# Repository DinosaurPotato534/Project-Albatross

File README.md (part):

# Project Albatross

The goal for the project was to create an autonomous plane capable of flying for hours off of solar power. Another big aspect is the ability to takeoff from water using a pontoon system mounted to a 4-bar linkage. The plane is going to be made from foam board and 3d prints. The wingspan is 90in and the length is roughly 6ft. 

https://cad.onshape.com/documents/cb4d8119196719dc9005cd1f/w/a50220c0795171ae93763f3d/e/ee41d6fe8c21d3f854f1676d?renderMode=0&uiState=6aa1fe8d3db98abb8ad60905

## Motivation
We wanted to explore the idea of multi-hour flight using solar power. Most rc planes have a relatively short flight time, but we wanted to try and expand on that. That is why we also added the pontoons, so it could recharge on the surface of water.

## Design

### Pontoons
The pontoon mechanism works by having two hollow 3D printed hulls swing out when landing. The reason we decided to put them on a swinging mechanism was that it would greatly reduce drag, and in turn air resistance. Just based on frontal area that's around a 25% increase in efficiency. They will be driven by a motor that will winch it up or down.

### Solar Panels
The solar panels just sit on the wing and will be wired to an MPPT board. They each generate around 3.5W in full sun, and there will be 17. It should be enough to sustain flight, but it will almost never get perfect lighting, so we will see. These sit on a 90in wing that has an 7in chord (not including the ailerons). Panels measure 125mm, so roughly 5in.

### Hull
Used a series of ribs inside to support a really thin outer shell of 3D print. These will slide down into their corresponding spots, making the structure much stronger. The front one also serves as the motor mount too.

## PCB
### Flight Controller
The flight controller was built with Ardupilot in mind, with multiple connectors allowing for different sensors to be modular and  swapped out. It is designed to take a 3 or 4S battery, and runs on an STM32F405RGT6. We are planning on using a GPS and a magnetometer but we have extra connector for different sensors if we want to add them going forward. We also have an IMU and pressure sensor on the board.

### MPPT Board
We made a full solar circuit, with a MPPT board and BMI. With this plane design we kept the wings relatively small. Only 17 solar panels could fit. With each solar panel proving roughly 0.6V the total voltage was roughly 10V. This is well below the standard voltage of a 4s battery, thus we needed a step up MPPT board. The market for this is miniscule and expensive leading our design to be useful as it functioned as both a step up and step down board depending on the solar array. However, our board also ended up being far to expensive to become justifiable. We decided to pivot to using a standard step down MPPT and increasing the solar area, as well as deceasing the battery voltage to a 3S.

## Assembly 

### The Plane
Most of the planes assembly consists of techniques similar to other rc planes. The wings are made from foam board "wrapped" around a dowel spar. They are made by cutting 3 slits across a sheet of foam board spaced out at 7in, 8iin, and 17 from one end. Then the paper layer of the foam board is peeled off for the top of the airfoil to create a better curve. The foam board is folded over the wing spar and three sections of these are connected.

The body is made from a dowel as the main structure of the hull, with 3d printed shells for aerodynamics and part containers. The slide onto the dowel and will be hot glued into place. Then the electronics are wired and placed into the nose cone of the 3d printed hull. The pontoons can then be mounted on they're hinges, which will be connected to n20 motor to swing up and down.
Solar panels will be mounted on the wing using a plastic wrap to hold them in place, while still allowing sunlight through.

### The PCB
Both the pcbs, especially the mppt board, are rather complex and have a lot of smd soldering. The use of a hot plate will be need and following the design the components will be soldered on. These boards will then be wired and hooked up to the rest of the planes electronics.

## BOM

| Description                                                  | Quantity |    Price | Link                                                                                                                                                                                                                                                                                                                                                                                                                                                                                                                                                                                                                                                                    |
| ------------------------------------------------------------ | -------: | -------: | ----------------------------------------------------------------------------------------------------------------------------------------------------------------------------------------------------------------------------------------------------------------------------------------------------------------------------------------------------------------------------------------------------------------------------------------------------------------------------------------------------------------------------------------------------------------------------------------------------------------------------------------------------------------------- |
| Main Brushless Motor                                         |        0 |    19.98 | [View](https://www.amazon.com/D2830-Brushless-Multi-Copter-Fixed-Wing-Helicopters/dp/B0D3DTQCS6?crid=1GIDDJS7T4YGM&dib=eyJ2IjoiMSJ9.AtVN6vy-8eWpAr1MRXuwIyZDgROcZ_Tzuz1vBoY-LQgoGHMikw6Aqbtr0vY9_g7-KdBo8Uc5qtG9Z2M4y7HJNJ-4DeF8kwkHgLJEmAUFDxmb91PZrz4W3htgwBpbw4BqP0INFkJTwgfE83IHLo2A6Yt1P7s4NWxooXJ_7hyRbZfiLSRV9Om79zQwpNE-6LewTQ_vMCWp6zsd65cN0q3pzUgZFKQl49tTeJsKrsUk_vwhCnAS4FoziM5t2XskwUUXPg0w_hbD3VEKizfJy3LNRxQ9HERiJKMdJODfD9-f40Y.mDKjGPO2-bY4kN_1C4PMB4SJw4Vj_UEMF7pvPhxdHXQ&dib_tag=se&keywords=4s%2Bbrushless%2Bmotor&qid=1787538403&s=industrial&sprefix=4s%2Bbrushless%2Bmoto%2Cindustrial%2C144&sr=1-24&th=1)                                       |
| Propeller                                                    |        0 |     9.19 | [View](https://www.amazon.com/FOCMKEAS-Propeller-Control-Quadcopter-Propellers/dp/B0F7LGSVNX?dib=eyJ2IjoiMSJ9.A6pEEgKzE0xpVNJD1XzkBh2nzCzQmoNq3ytnVg6CN18DSJCYAb_vIOQs6C8UpuIxUIBGOFXvnDEB_UkNs5OgI2uLLwH9465pMMq5V0m_Dc9-5lnfrtW4XxR0hVYtef-Q3eX9Ex-b_6jeFyqg4qao58oj_oSJQ67rCSTJcOPaGaEuolYwWYajsof5d2b4Q7oDYOMhOJqfl2KeGGB-YOsVRt_N_G7Wvj5ITrCs1dr519pMPs-xR864BLOs0i2SqKWhch3QZd_lyTU7AmSTrIm3AY6-M7YS4UeShy5_y6pB76uU.ozcTE64lZMBamYODjHXiUzZvMs33qJ17Fo1byxuyLn0&dib_tag=se&keywords=10x7%2Bpropeller&qid=1787538510&sr=8-9&th=1)                                                                                                                                 |
| Light Weight PLA                                             |        1 |    29.99 | [View](https://www.amazon.com/Polymaker-PolyLite-LW-PLA-1-75mm-800g/dp/B09H2SC1CX?crid=2132M6YWZ9EGL&dib=eyJ2IjoiMSJ9.EbFv4lznFsPcWRDS9TjkviMWlq_K4jqpkA8IQc7o2zDEebKpblPqLRmth953MziS7uqHudJ0SZ3s5wBnAt_yUrxKvtQmWUkzZDUHRLlRxhPQMmJGF5JgJkjI19orItGwAG-fORcVH57sKaYh6ABwSmNhR0hW-JCWFJVTA7df6mxN11L5wEezJSx71Ra0gn5ADS7o05-v34wEVmZvxTj3QMUajjPENJMn1u_jx4HQ0n0.XZf55xAyfc2s93rCVnJll9koOeH9xDjBtNictLozpg4&dib_tag=se&keywords=pla%2Baero&qid=1787525308&sprefix=pla%2Baero%2Caps%2C175&sr=8-2&th=1)                                                                                                                                                                 |
| Solar Panels                                                 |       30 |        4 | [View](https://www.ebay.com/itm/382873833299?_trksid=p2332490.c101224.m-1&var=651906635231)                                                                                                                                                                                                                                                                                                                                                                                                                                                                                                                                                                             |
| Servos (5 Pack)                                              |        1 |    15.99 | [View](https://www.amazon.com/dp/B0BWJ2CK9D?_encoding=UTF8&th=1)                                                                                                                                                                                                                                                                                                                                                                                                                                                                                                                                                                                                        |
| Servo Extention Cables                                       |        1 |     9.99 | [View](https://www.amazon.com/ACEIRMC-Extension-Connector-Airplanes-Control/dp/B0CP7FRV31?crid=208A8HM7J7RMB&dib=eyJ2IjoiMSJ9.zvspaGyYEhj8FE188_ucmxEkKO9qxdxkeWBVjVOxg_IdOeuFNdGl7vn5_YA_3SkekBpo1C4ZVZeYne-sWa-vqcT14DQGpfkZP0DvSsxYqCkKgQiqMDOEiCSFFEm6DgK3rqWCAZoQL5KlCa5mTqUZ2ex7WquiyLc5CjRFcVyx7MRTT2iRXcr1xalmlWvPcaOSW3QRbxB1vWPW9z5XEMp2abnEaBUddNU7IUBYtHoYaUeh_4k-P5CyB4RuSx_zgH8jz7q1C9rbM7gXJz2oLb_1u9YX6dsfYdR8L4PDelta2Ic.q6GoTBJ_aluZ2bmCM-GL7KpXotR3rhAZuRiR03xYp-Y&dib_tag=se&keywords=servo%2Bextension%2Bcable%2B3ft&qid=1787525999&sprefix=servo%2Bextension%2Bcable%2B3ft%2Caps%2C156&sr=8-2&th=1)                                               |
| 3S Lipo                                                      |        0 |    16.99 | [View](https://www.amazon.com/2200mAh-Connector-Airplane-Quadcopter-Helicopter/dp/B08CZF373Y?dib=eyJ2IjoiMSJ9.qVFbEjwkpjGPTIbNqqaG4vhhEhuTYIhbIrznxJf2mWbGQFAQZzQvMC-RFV3-_m0Y3fUMGU2WUniptrScL0GNg0JNWvpu92oegfyhtbsOfVlIXlQ-MSGKUgVLKmpeuwx3UI1lsvJuu8vqa-Yaq4HsqnQAZZ_Rz_IvS5CB1vaPLZo0VIJ8n6EhUtJ7-DbkXdtaIhPBBi96NDbnM-Gm8rh9aLTVWOSHBg1nrYiUrKQ3GgO3EjhKp2QWHQe2iZsrDUKseEFkoB9d_mDGmAwJTdDD2BOaxg-PfcvtzBMpGu8Q-8.kPC3qnyTph9ywtksvaFng7sRWRmlsHQLAdpGe4SUKuI&dib_tag=se&keywords=3s%2Blipo%2Bbattery%2B2200mah%2Bturnigy&qid=1788917182&sr=8-5&th=1)                                                                                                            |
| ESC                                                          |        0 |     28.4 | [View](https://www.amazon.com/60A-Brushless-Fixed-Wing-Aircraft-Helicopter/dp/B0FRM7X984?crid=3PJRS2ICQ8PJD&dib=eyJ2IjoiMSJ9.l-i8O1etdcDAwANXbMuoWiZWPcCDAv0Sbts3AtoG4644KeM131bYEzrw-p2MOpDivXIBVtqrIHys9zYjqJ12LKnK6i-6AH8XN9EJTKXhXk6bnEsInO310qC9xtRnb-KxAyLtBdO-nKIXAzmh6S25dI1q8qE13uXMczSF6lAoa4Z5NEnQ1c-VgTorYn7Om1HT8OKtg7QFZ9L8LORe08OILE3gtEbHjzeyqic_LyjKrPWg9aB3qZkXp0HWgDVTno_lIJrRG5CHcl-eH1EkQ6-XxLoF0CTAm4u7tXZE4JOihRc.F29bWjkF8PrGOvVfpu0PWkPe3OBKBhs2UlFD32E6XW8&dib_tag=se&keywords=60A%2Besc&qid=1787538359&sprefix=60a%2Bes%2Caps%2C204&sr=8-4&th=1)                                                                                             |
| Heat Set Inserts                                             |        1 |     4.99 | [View](https://www.amazon.com/Aoserge-100Pcs-Brass-Heat-Inserts/dp/B0FM45X5TD?crid=18SC6KZP9OQV&dib=eyJ2IjoiMSJ9.yMovo3L8gJsoYK8w4IEzTWAA8Pa8BA9cJIQ-iAF8utzPJ714NxCnewEAb7-vQQ4wjrNfGFI7i-OyntuQi7irDqRP6uR-vwBS8VsjYbYfnEGw1HEHWc_urtRw7aOZabJ8nMm7X1PGJRnSm_dumVbfvMLHscQXXEKbt6OXNfPWSSik5vOfFX9qPY9pHfWj4SHEL0ygbkMKETaEilfUxx_5VjPdDVNT5e97h0AJBQlPIaQ.5RN2Lr60uWhE16Ea_KMSffw7Fy3fc5X4_u3aus6Fmds&dib_tag=se&keywords=heat%2Bset%2Binserts&qid=1788233777&refinements=p_36%3A-1000&rnid=386419011&sprefix=heat%2Bset%2Binsert%2Caps%2C177&sr=8-8&th=1)                                                                                                           |
| M3 Screws                                                    |        1 |     6.99 | [View](https://www.amazon.com/Machine-Assorted-Assortment-Stainless-Threaded/dp/B0DFWX8F36?crid=2IMXPAP1DEIAP&dib=eyJ2IjoiMSJ9.yZ4b1PXj7_4Gv5y9TnkcPHKxO-JQ9HyV9zOqDs1Fm5YNqA9myOSVzQR86Kytn6L07abLABHcaVdUCsevvHmGTXOa28JjPYt_5xii7wxPjRW9afO-sCb8yxQ4SSXCAAmo9bffwnMVAzJu2TboclRhZvmMOorqYb0dWacgTGgbutoSSJYu1r2_nygjP9LcBysSyQC3k7f4e7l_HnsZ61rrlNLoYdkTnklYXdqPEj5ZLEU.NHmRGP9EbYvQucNLRHm8Z_QKjKLUAvDfJK4pTsFrj0Y&dib_tag=se&keywords=m3%2Bscrews&qid=1787538716&refinements=p_36%3A-1000&rnid=2661611011&sprefix=m3%2Bscrew%2Caps%2C168&sr=8-9&th=1)                                                                                                              |
| Controller                                                   |        0 |    54.89 | [View](https://www.amazon.com/FLYSKY-Transmitter-Controller-Receiver-Upgrade/dp/B07Z8VCB45?crid=31XOXYXMOF57J&dib=eyJ2IjoiMSJ9.oYVOZgIKCn7QHiQW_sPBdqCzg8t7x423ixB_IW4cyeVR8NzFLb4Va8IOe6aXXys3DgsJLeYg0AZj4C6nYi5yfUcnhJPpvlJfRvaaQPgnwUMt_mnDe2qD3gG-DdXs-hZiZr7JC06yUwYZu2FwEhZMYXUMUlfIZ3HLRCX-9MHtBgzPtYGTfMZA61y8FiqHdAbDZFId_eyTI-cYJqWUszTLyqKt7BXOan2ybAT59q5ePnzmNrsKFerFJt5INTKZUfP-MXZW1UjR8EVU4ZrsCfYvvbbefuqou7SJWZUwxCtYB74.GyGO-L0K5NV1BGEOLjfxkipUgwNBX3knqvS8UBxhQLE&dib_tag=se&keywords=fly+sky+controller&qid=1787538836&sprefix=fly+sky+co%2Caps%2C176&sr=8-1)                                                                                     |
| Foam Board                                                   |       10 |     1.25 | [View](https://www.dollartree.com/readi-board-white-foam-boards/809955)                                                                                                                                                                                                                                                                                                                                                                                                                                                                                                                                                                                                 |
| N20 Motor                                                    |        4 |     4.17 | [View](https://www.aliexpress.us/item/3256803908995996.html?spm=a2g0o.productlist.main.1.204626f5A7Jdmy&algo_pvid=8b3a0dbe-85eb-467c-8fe9-f87f66337553&algo_exp_id=8b3a0dbe-85eb-467c-8fe9-f87f66337553-0&pdp_ext_f=%7B%22order%22%3A%221694%22%2C%22eval%22%3A%221%22%2C%22fromPage%22%3A%22search%22%7D&pdp_npi=6%40dis%21USD%213.68%210.99%21%21%213.68%210.99%21%40210328c017889213388988109e0e7d%2112000028016789215%21sea%21US%210%21ABX%211%210%21n_tag%3A-29910%3Bd%3Ac2c1a869%3Bm03_new_user%3A-29895%3BpisId%3A5000000210782938&curPageLogUid=oM71zmsPOiT8&utparam-url=scene%3Asearch%7Cquery_from%3A%7Cx_object_id%3A1005004095310748%7C_p_origin_prod%3A)   |
| GPS                                                          |        1 |     15.9 | [View](https://robofusion.net/products/mg-a01-gps-module)                                                                                                                                                                                                                                                                                                                                                                                                                                                                                                                                                                                                               |
| Telemetry                                                    |        1 |     65.9 | [View](https://robofusion.net/products/micoair-lr900-p-915mhz-lora-telemetry-radio-for-pixhawk-ardupilot-px4-1w-fhss-flagship-long-range-pair?variant=54111278530879)                                                                                                                                                                                                                                                                                                                                                                                                                                                                                                   |
| BMS                                                          |        1 |     1.13 | [View](https://www.aliexpress.us/item/3256807501448998.html?spm=a2g0o.productlist.main.24.77ec3d62baKU9j&algo_pvid=bad08f0c-8228-4e05-bf4c-bcd4cd963110&algo_exp_id=bad08f0c-8228-4e05-bf4c-bcd4cd963110-21&pdp_ext_f=%7B%22order%22%3A%22928%22%2C%22eval%22%3A%221%22%2C%22fromPage%22%3A%22search%22%7D&pdp_npi=6%40dis%21USD%211.13%210.99%21%21%217.56%216.62%21%402101c4b817889206645041384e0e0f%2112000041841194925%21sea%21US%210%21ABX%211%210%21n_tag%3A-29910%3Bd%3Ac2c1a869%3Bm03_new_user%3A-29895%3BpisId%3A5000000210782938&curPageLogUid=EdmXCWhx64s9&utparam-url=scene%3Asearch%7Cquery_from%3A%7Cx_object_id%3A1005007687763750%7C_p_origin_prod%3A)  |
| MPPT Board                                                   |        1 |    20.41 | [View](https://www.aliexpress.us/item/3256810455381147.html?spm=a2g0o.productlist.main.5.1764tsWXtsWXhf&algo_pvid=96684140-d778-43dc-ac98-f4994373f856&algo_exp_id=96684140-d778-43dc-ac98-f4994373f856-4&pdp_ext_f=%7B%22order%22%3A%2212%22%2C%22eval%22%3A%22%22%2C%22fromPage%22%3A%22search%22%7D&pdp_npi=6%40dis%21USD%2120.41%2113.28%21%21%21136.26%2188.66%21%402101ca9517889202540843342e0eab%2112000053059870601%21sea%21US%210%21ABX%211%210%21n_tag%3A-29910%3Bd%3Ac2c1a869%3Bm03_new_user%3A-29895%3BpisId%3A5000000210782933&curPageLogUid=7y9B1Ewqa6k0&utparam-url=scene%3Asearch%7Cquery_from%3A%7Cx_object_id%3A1005010641695899%7C_p_origin_prod%3A) |
| passive piezo                                                |        5 |   0.4017 | [View](https://www.lcsc.com/product-detail/C128650.html?s_z=n_q_C128650&globalKeyword=C128650)                                                                                                                                                                                                                                                                                                                                                                                                                                                                                                                                                                          |
| 100u/35V poly                                                |       50 |   0.0139 | [View](https://www.lcsc.com/product-detail/C14663.html?s_z=n_q_CC0603KRX7R9BB104&spm=wm.fly.bg.0.xh&lcsc_vid=ElFaA1QDFFgKXlQHFFINU1JeFlZaUF0FQFNdXlUFEgUxVlNeT1ZcVldQRlleXzsOAxUeFF5JWBYZEEoKFBINSQcJGk4%3D)                                                                                                                                                                                                                                                                                                                                                                                                                                                            |
| 100n/50V 0603                                                |       10 |   0.2003 | [View](https://www.lcsc.com/product-detail/Multilayer-Ceramic-Capacitors-MLCC-SMD-SMT_Taiyo-Yuden-TMK325BJ106KN-T_C92834.html)                                                                                                                                                                                                                                                                                                                                                                                                                                                                                                                                          |
| 10u/25V 1210                                                 |       10 |   0.2257 | [View](https://www.lcsc.com/product-detail/C92771.html?s_z=n_q_Taiyo%2520Yuden%2520EMK325BJ226MD-T&spm=wm.fly.bg.0.xh&lcsc_vid=FANdVwJVQgMLV11TTlQPX1UHRlFcBlFQRlEMBFYDE1kxVlNeT1ddUlVRQFZYUDsOAxUeFF5JWBYZEEoKFBINSQcJGk4eFQsCAgIaSgADAwAHC0sLAg0aDggHDgQcSgcDBQADDgdLFAAeBgcPAw4cFEkLGwINShcLE0wdChA5AwAHHgtLDhQKAgpLEgwFVFZTFQtcVVILE0waOCdfRVZZVkoOAwwC)                                                                                                                                                                                                                                                                                                            |
| 22u/16V 1210                                                 |       20 |   0.0291 | [View](https://www.lcsc.com/product-detail/multilayer-ceramic-capacitors-mlcc-smd-smt_cctc-tcc0805x7r105k250ft_C282734.html)                                                                                                                                                                                                                                                                                                                                                                                                                                                                                                                                            |
| 1u 0805                                                      |      100 |    0.005 | [View](https://www.lcsc.com/product-detail/C60474.html)                                                                                                                                                                                                                                                                                                                                                                                                                                                                                                                                                                                                                 |
| 100n 0402                                                    |       10 |   0.0614 | [View](https://www.lcsc.com/product-detail/C132176.html?s_z=n_q_CC0805KKX5R7BB475&spm=wm.fly.bg.0.xh&lcsc_vid=ElFaA1QDFFgKXlQHFFINU1JeFlZaUF0FQFNdXlUFEgUxVlNeT1ZcVldQRlFURFFcVDsOAxUeFF5JWBYZEEoKFBINSQcJGk4NBhADEA4cHktXRlVcSQwSGg0%3D)                                                                                                                                                                                                                                                                                                                                                                                                                               |
| 4.7u 0805                                                    |       50 |   0.0138 | [View](https://www.lcsc.com/product-detail/Multilayer-Ceramic-Capacitors-MLCC-SMD-SMT_1uF-105-10-16V_C93816.html)                                                                                                                                                                                                                                                                                                                                                                                                                                                                                                                                                       |
| 1u 0603                                                      |       50 |   0.0191 | [View](https://www.lcsc.com/product-detail/C23630.html?is_substitute=1&original_product_code=C20241888&original_unit_price=0.1047)                                                                                                                                                                                                                                                                                                                                                                                                                                                                                                                                      |
| 2.2u 0603                                                    |      100 |    0.007 | [View](https://www.lcsc.com/product-detail/C342941.html?s_z=n_q_CGA2B2C0G1H100DT0Y0F&spm=wm.fly.bg.0.xh&lcsc_vid=ElFaA1QDFFgKXlQHFFINU1JeFlZaUF0FQFNdXlUFEgUxVlNeT1ZcVlBTRVBeUDsOAxUeFF5JWBYZEEoKFBINSQcJGk4NBhADEA4cHktXRlVcSQwSGg0%3D)                                                                                                                                                                                                                                                                                                                                                                                                                                |
| 10p 0402                                                     |       10 |   0.0803 | [View](https://www.lcsc.com/product-detail/C96179.html)                                                                                                                                                                                                                                                                                                                                                                                                                                                                                                                                                                                                                 |
| 470u/16V 8x10.5                                              |        5 |   0.2003 | [View](https://www.lcsc.com/product-detail/Multilayer-Ceramic-Capacitors-MLCC-SMD-SMT_Taiyo-Yuden-TMK325BJ106KN-T_C92834.html)                                                                                                                                                                                                                                                                                                                                                                                                                                                                                                                                          |
| 10u 1210                                                     |        5 |   0.1813 | [View](https://www.lcsc.com/product-detail/C318781.html?s_z=n_q_C318781&globalKeyword=C318781)                                                                                                                                                                                                                                                                                                                                                                                                                                                                                                                                                                          |
| 10u/16V 1210                                                 |       20 |     0.04 | [View](https://www.lcsc.com/product-detail/C386014.html?is_substitute=1&lcsc_vid=RAQKXlVQQ1kPUwcDRFRcVlJVT1VfAwVSTgRfUVVSRlkxVlNeQVVdVVVVQFFXUDtW&original_product_code=C363943&original_unit_price=0.0898)                                                                                                                                                                                                                                                                                                                                                                                                                                                             |
| 2.2u/6.3V 0603                                               |       10 |    0.061 | [View](https://www.digikey.com/en/products/detail/kemet/C0603C103K5RACTU/411090)                                                                                                                                                                                                                                                                                                                                                                                                                                                                                                                                                                                        |
| 10n/16V 0603                                                 |        4 |      0.5 | [View](https://www.digikey.com/en/products/detail/littelfuse-inc/SMBJ20A/285988)                                                                                                                                                                                                                                                                                                                                                                                                                                                                                                                                                                                        |
| SMBJ20A                                                      |        5 |     0.16 | [View](https://www.digikey.com/en/products/detail/diotec-semiconductor/BAT54C/13163831)                                                                                                                                                                                                                                                                                                                                                                                                                                                                                                                                                                                 |
| BAT54C                                                       |        1 |   2.7641 | [View](https://www.lcsc.com/product-detail/C1512043.html?s_z=n_q_1206L300%252F12SLYR&spm=wm.fly.bg.0.xh&lcsc_vid=ElFaA1QDFFgKXlQHFFINU1JeFlZaUF0FQFNdXlUFEgUxVlNeT1ZcVlBeRlBYVTsOAxUeFF5JWBYZEEoKFBINSQcJGk4NBhADEA4cHktXRlVcSQwSGg0%3D)                                                                                                                                                                                                                                                                                                                                                                                                                                |
| Fuse 3A 1206                                                 |       10 |   0.0283 | [View](https://www.lcsc.com/product-detail/C21519.html?s_z=n_q_MPZ2012S601AT000&spm=wm.fly.bg.0.xh&lcsc_vid=ElFaA1QDFFgKXlQHFFINU1JeFlZaUF0FQFNdXlUFEgUxVlNeVldURFFcVDsOAxUeFF5JWBYZEEoKFBINSQcJGk4NBhADEA4cHktXRVZADxALGw%3D%3D)                                                                                                                                                                                                                                                                                                                                                                                                                                       |
| 600R@100MHz 0805                                             |        3 |     0.65 | [View](https://www.lcsc.com/product-detail/C428722.html)                                                                                                                                                                                                                                                                                                                                                                                                                                                                                                                                                                                                                |
| USB4085                                                      |        1 |     0.91 | [View](https://www.digikey.com/en/products/detail/gct/USB4085-GF-A/9859662?s=N4IgTCBcDaIOIGEAqACAqgZQEIBYAMAHAKwgC6AvkA)                                                                                                                                                                                                                                                                                                                                                                                                                                                                                                                                                |
| Connector_PinHeader_1.27mm:PinHeader_1x06_P1.27mm_Vertical   |        5 |   0.2606 | [View](https://www.lcsc.com/product-detail/C3408.html?s_z=n_q_C3408&globalKeyword=C3408)                                                                                                                                                                                                                                                                                                                                                                                                                                                                                                                                                                                |
| Connector_PinHeader_2.54mm:PinHeader_1x03_P2.54mm_Vertical   |       20 |   0.0278 | [View](https://www.lcsc.com/product-detail/C49257.html)                                                                                                                                                                                                                                                                                                                                                                                                                                                                                                                                                                                                                 |
| Connector_JST:JST_PH_S2B-PH-K_1x02_P2.00mm_Horizontal        |       10 |   0.0669 | [View](https://www.lcsc.com/product-detail/C265016.html)                                                                                                                                                                                                                                                                                                                                                                                                                                                                                                                                                                                                                |
| Connector_JST:JST_GH_BM06B-GHS-TBT_1x06-1MP_P1.25mm_Vertical |        5 |   0.3036 | [View](https://www.lcsc.com/product-detail/C189892.html)                                                                                                                                                                                                                                                                                                                                                                                                                                                                                                                                                                                                                |
| Connector_JST:JST_GH_BM04B-GHS-TBT_1x04-1MP_P1.25mm_Vertical |       10 |   0.1301 | [View](https://www.lcsc.com/product-detail/C3011955.html?s_z=n_q_C3011955&globalKeyword=C3011955)                                                                                                                                                                                                                                                                                                                                                                                                                                                                                                                                                                       |
| Connector_JST:JST_GH_BM03B-GHS-TBT_1x03-1MP_P1.25mm_Vertical |        5 |   0.2223 | [View](https://www.lcsc.com/product-detail/C161691.html)                                                                                                                                                                                                                                                                                                                                                                                                                                                                                                                                                                                                                |
| Connector_JST:JST_GH_BM05B-GHS-TBT_1x05-1MP_P1.25mm_Vertical |        1 |   0.5359 | [View](https://www.lcsc.com/product-detail/C189891.html)                                                                                                                                                                                                                                                                                                                                                                                                                                                                                                                                                                                                                |
| 10uH SRP7028A-100M                                           |        1 |      1.1 | [View](https://www.digikey.com/en/products/detail/bourns-inc/SRP7028A-100M/4876641?s=N4IgTCBcDaIMoCUAKB2ADGAHAQQLQEY00BZEAXQF8g)                                                                                                                                                                                                                                                                                                                                                                                                                                                                                                                                        |
| 6.8uH SRP1245A-6R8M                                          |        2 |     1.47 | [View](https://www.digikey.com/en/products/detail/bourns-inc/SRP1245A-6R8M/4876614?s=N4IgTCBcDaIEIHsCuAnAdgZwAQGUBKACgIxgAsArAIIC0AbHgBwCyIAugL5A)                                                                                                                                                                                                                                                                                                                                                                                                                                                                                                                      |
| red LED_0603                                                 |        2 |     0.14 | [View](https://www.digikey.com/en/products/detail/liteon/LTST-C190KRKT/386817)                                                                                                                                                                                                                                                                                                                                                                                                                                                                                                                                                                                          |
| blue LED_0603                                                |        2 |     0.16 | [View](https://www.digikey.com/en/products/detail/w%C3%BCrth-elektronik/150060BS75000/4489895)                                                                                                                                                                                                                                                                                                                                                                                                                                                                                                                                                                          |
| green PWR LED_0603                                           |        2 |     0.14 | [View](https://www.digikey.com/en/products/detail/liteon/LTST-C190GKT/269230)                                                                                                                                                                                                                                                                                                                                                                                                                                                                                                                                                                                           |
| 2N7002                                                       |       50 |   0.0112 | [View](https://www.lcsc.com/product-detail/C916396.html?s_z=n_q_x_2N7002&spm=wm.ssy.em.0.tz&lcsc_vid=FANdVwJVQgMLV11TTlQPX1UHRlFcBlFQRlEMBFYDE1kxVlNeT1dcX1VVRFFXVTsOAxUeFF5JWBYZEEoKFBINSQcJGk4dAgUUFAk%3D)                                                                                                                                                                                                                                                                                                                                                                                                                                                            |
| 1m 2512                                                      |       20 |   0.0512 | [View](https://www.lcsc.com/product-detail/C55485.html?s_z=n_q_C55485&globalKeyword=C55485)                                                                                                                                                                                                                                                                                                                                                                                                                                                                                                                                                                             |
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
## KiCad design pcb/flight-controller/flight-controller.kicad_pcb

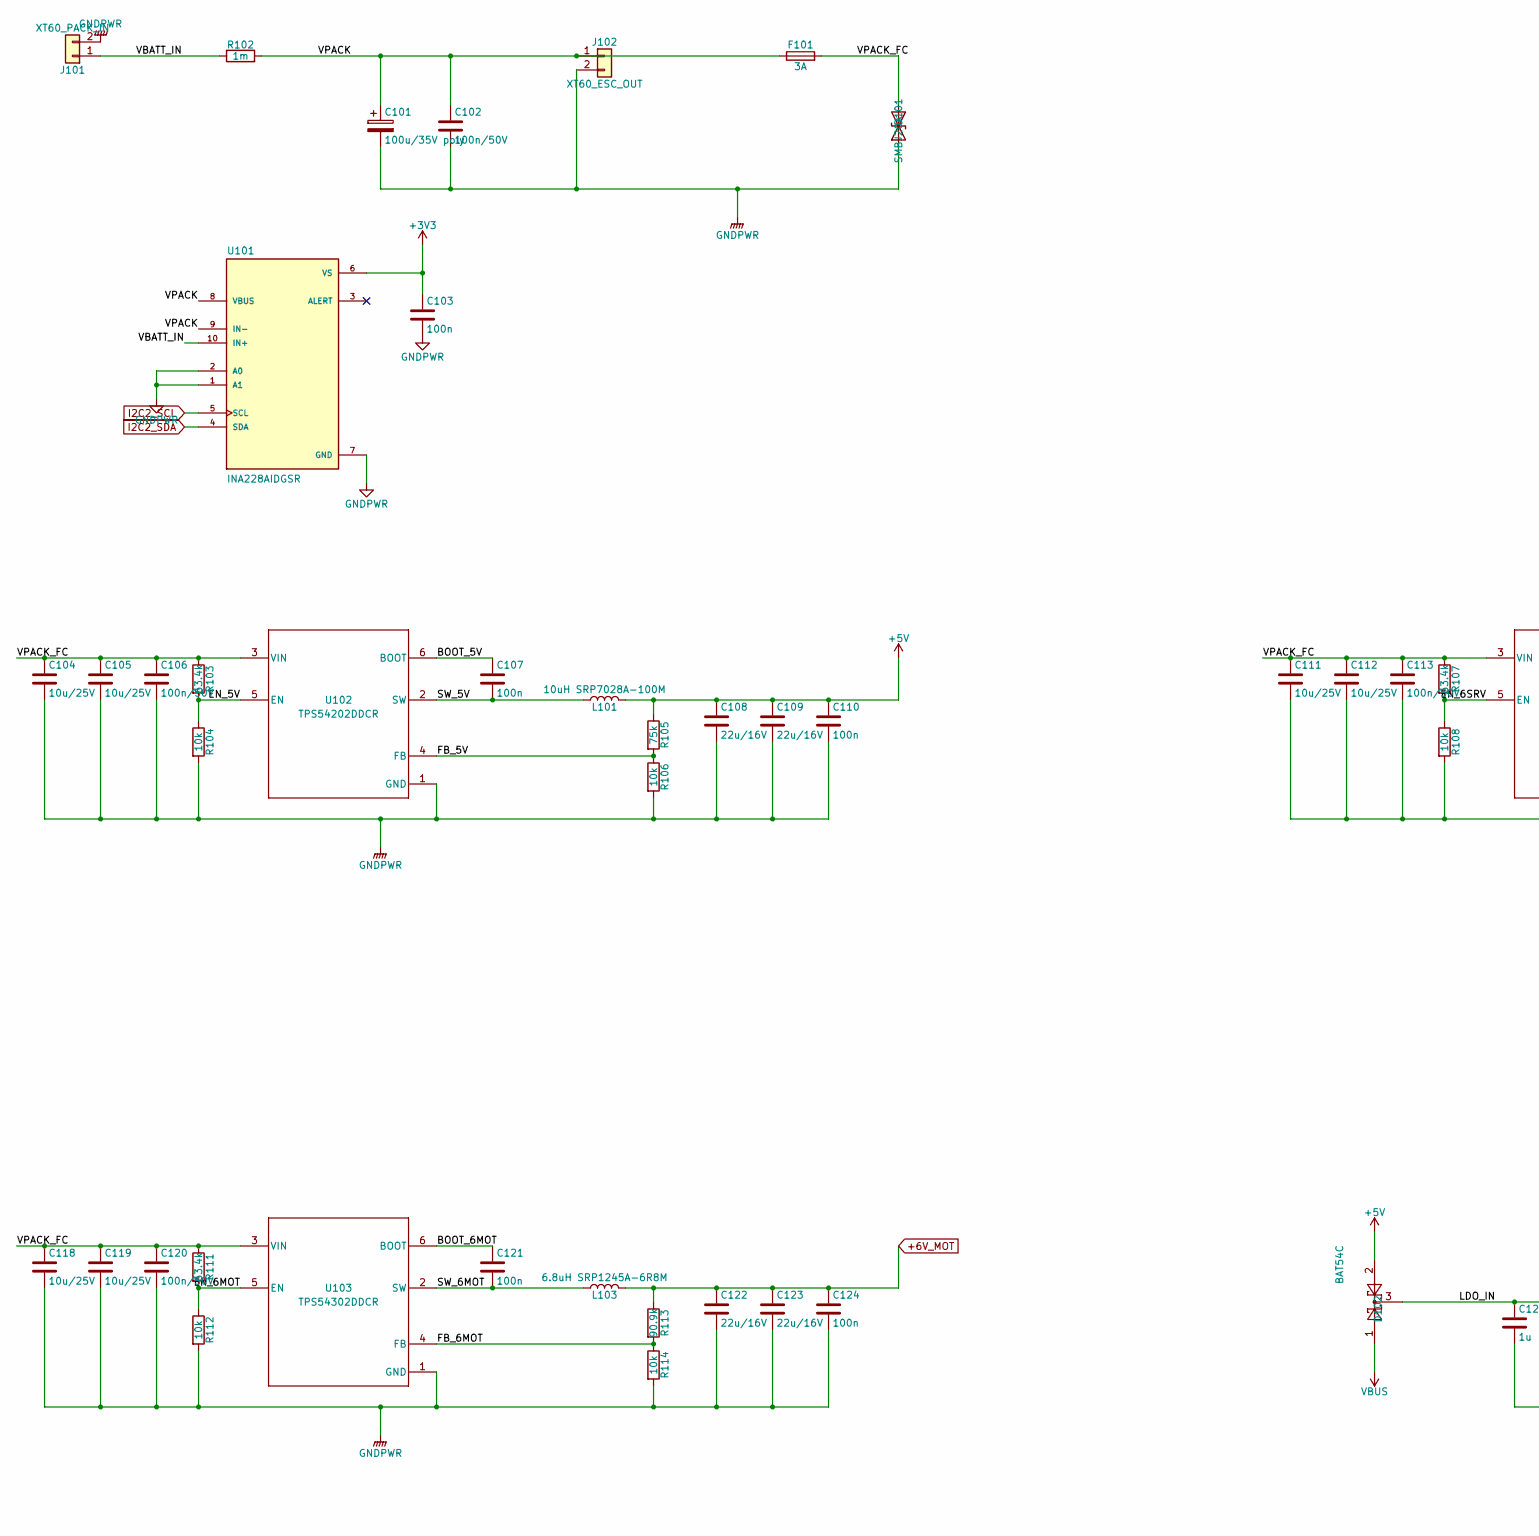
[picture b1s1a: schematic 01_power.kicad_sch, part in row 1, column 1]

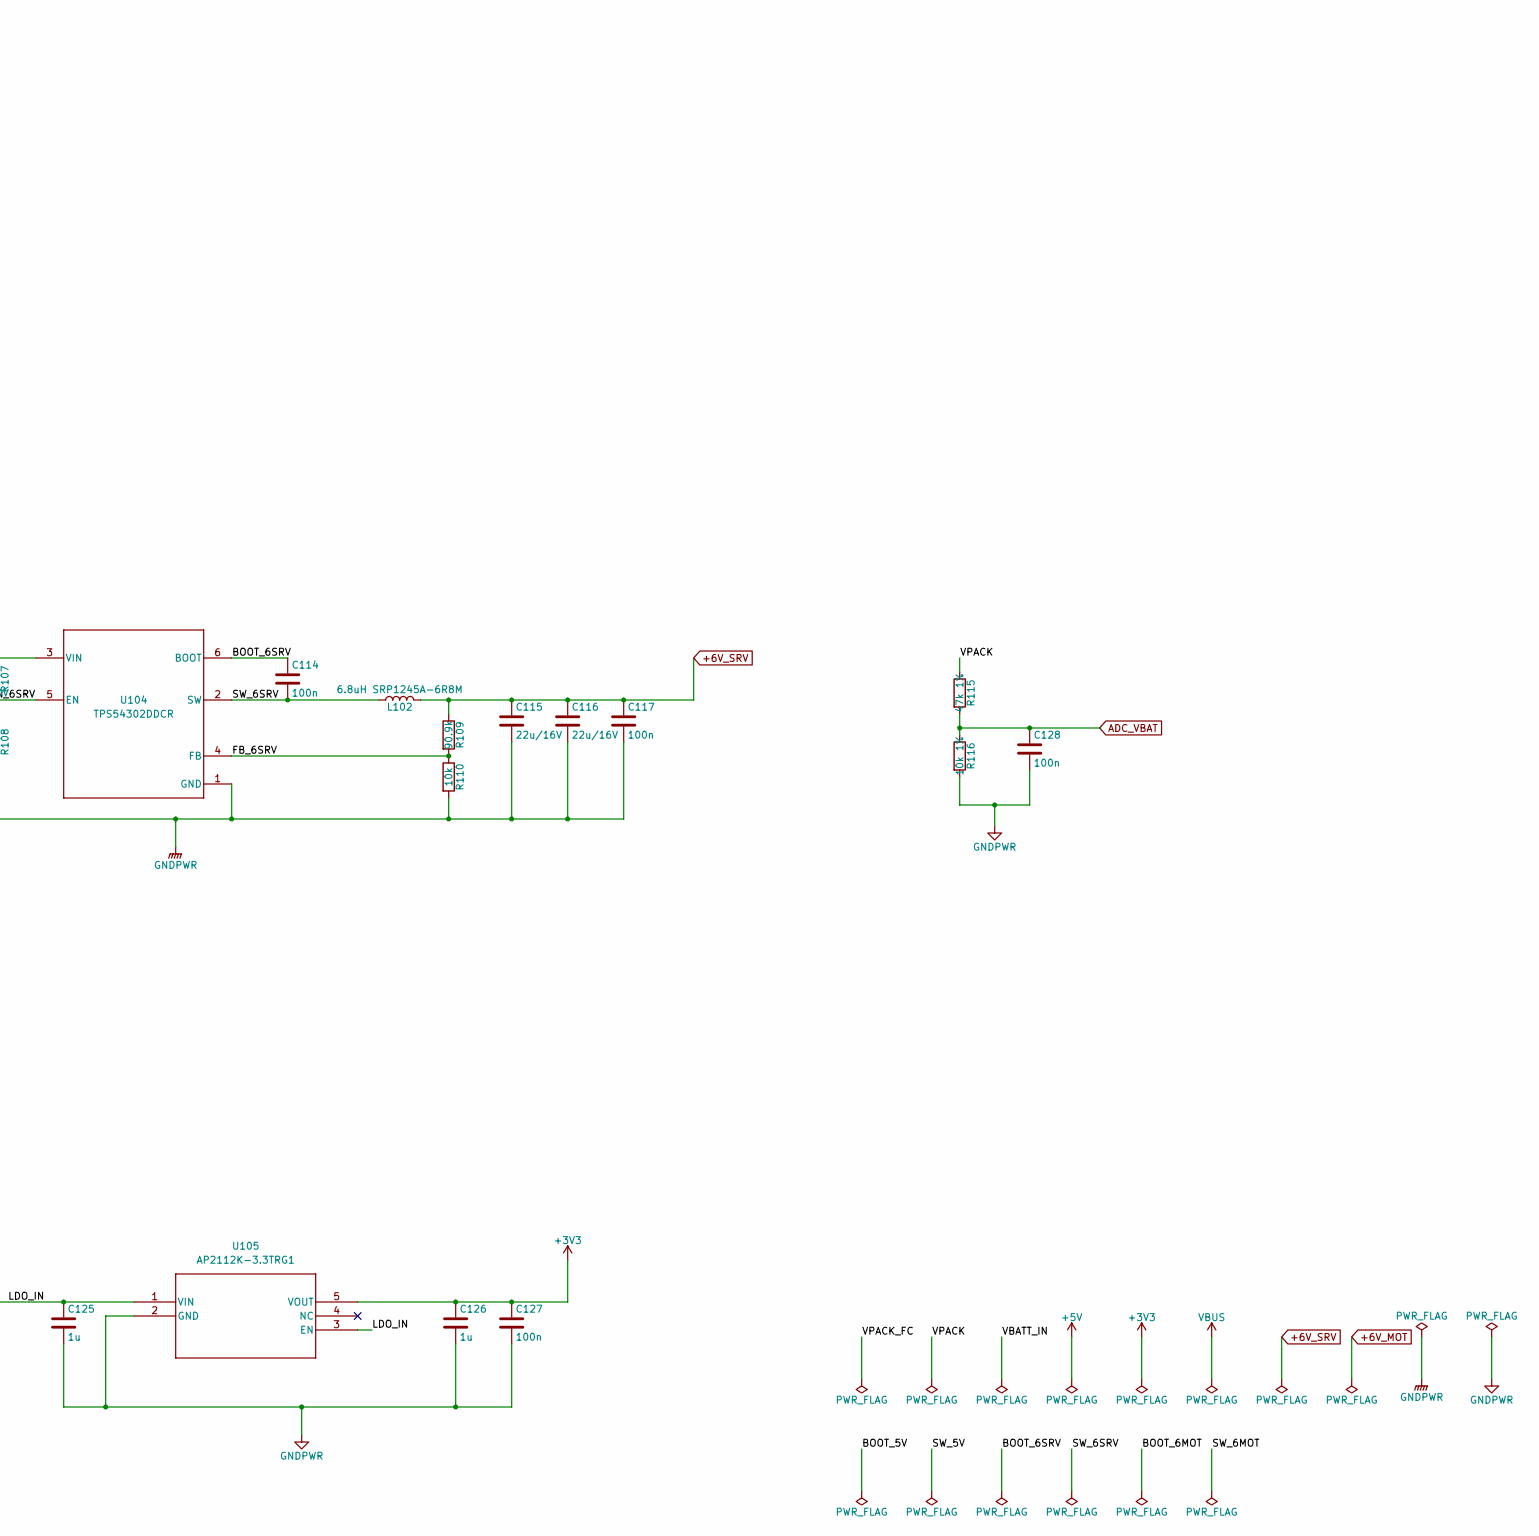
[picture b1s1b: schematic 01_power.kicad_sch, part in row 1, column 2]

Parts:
C101: 100u/35V poly; CP_EIA-7343-31_Kemet-D
C102, C106, C113, C120: 100n/50V; C_0603_1608Metric
C103, C107, C110, C114, C117, C121, C124, C127, C128: 100n; C_0603_1608Metric
C104, C105, C111, C112, C118, C119: 10u/25V; C_1210_3225Metric
C108, C109, C115, C116, C122, C123: 22u/16V; C_1210_3225Metric
C125, C126: 1u; C_0805_2012Metric
D101: SMBJ20A; D_SMB
D102: BAT54C; SOT-23
F101: 3A; Fuse_1206_3216Metric
J101: XT60_PACK_IN; AMASS_XT60PW-F_1x02_P7.20mm_Horizontal
J102: XT60_ESC_OUT; AMASS_XT60PW-F_1x02_P7.20mm_Horizontal
L101: 10uH SRP7028A-100M; L_Bourns_SRP7028A_7.3x6.6mm
L102, L103: 6.8uH SRP1245A-6R8M; L_Bourns_SRP1245A
R102: 1m; R_2512_6332Metric
R103, R107, R111: 63.4k; R_0603_1608Metric
R104, R106, R108, R110, R112, R114: 10k; R_0603_1608Metric
R105: 75k; R_0603_1608Metric
R109, R113: 90.9k; R_0603_1608Metric
R115: 47k 1%; R_0603_1608Metric
R116: 10k 1%; R_0603_1608Metric
U101: INA228AIDGSR; SOP50P490X110-10N
U102: TPS54202DDCR; DDC0006A_N
U103, U104: TPS54302DDCR; DDC0006A_N
U105: AP2112K-3.3TRG1; SOT_RG1_DIO

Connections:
/01_POWER/EN_5V: R103.2, R104.1, U102.5 (EN)
/01_POWER/EN_6MOT: R111.2, R112.1, U103.5 (EN)
/01_POWER/EN_6SRV: R107.2, R108.1, U104.5 (EN)
/01_POWER/FB_5V: R105.2, R106.1, U102.4 (FB)
/01_POWER/FB_6MOT: R113.2, R114.1, U103.4 (FB)
/01_POWER/FB_6SRV: R109.2, R110.1, U104.4 (FB)
/01_POWER/LDO_IN: C125.1, D102.3, U105.1 (VIN), U105.3 (EN)
ADC_VBAT: C128.1, R115.2, R116.1; also elsewhere on the board
I2C2_SCL: U101.5 (SCL); also elsewhere on the board
I2C2_SDA: U101.4 (SDA); also elsewhere on the board

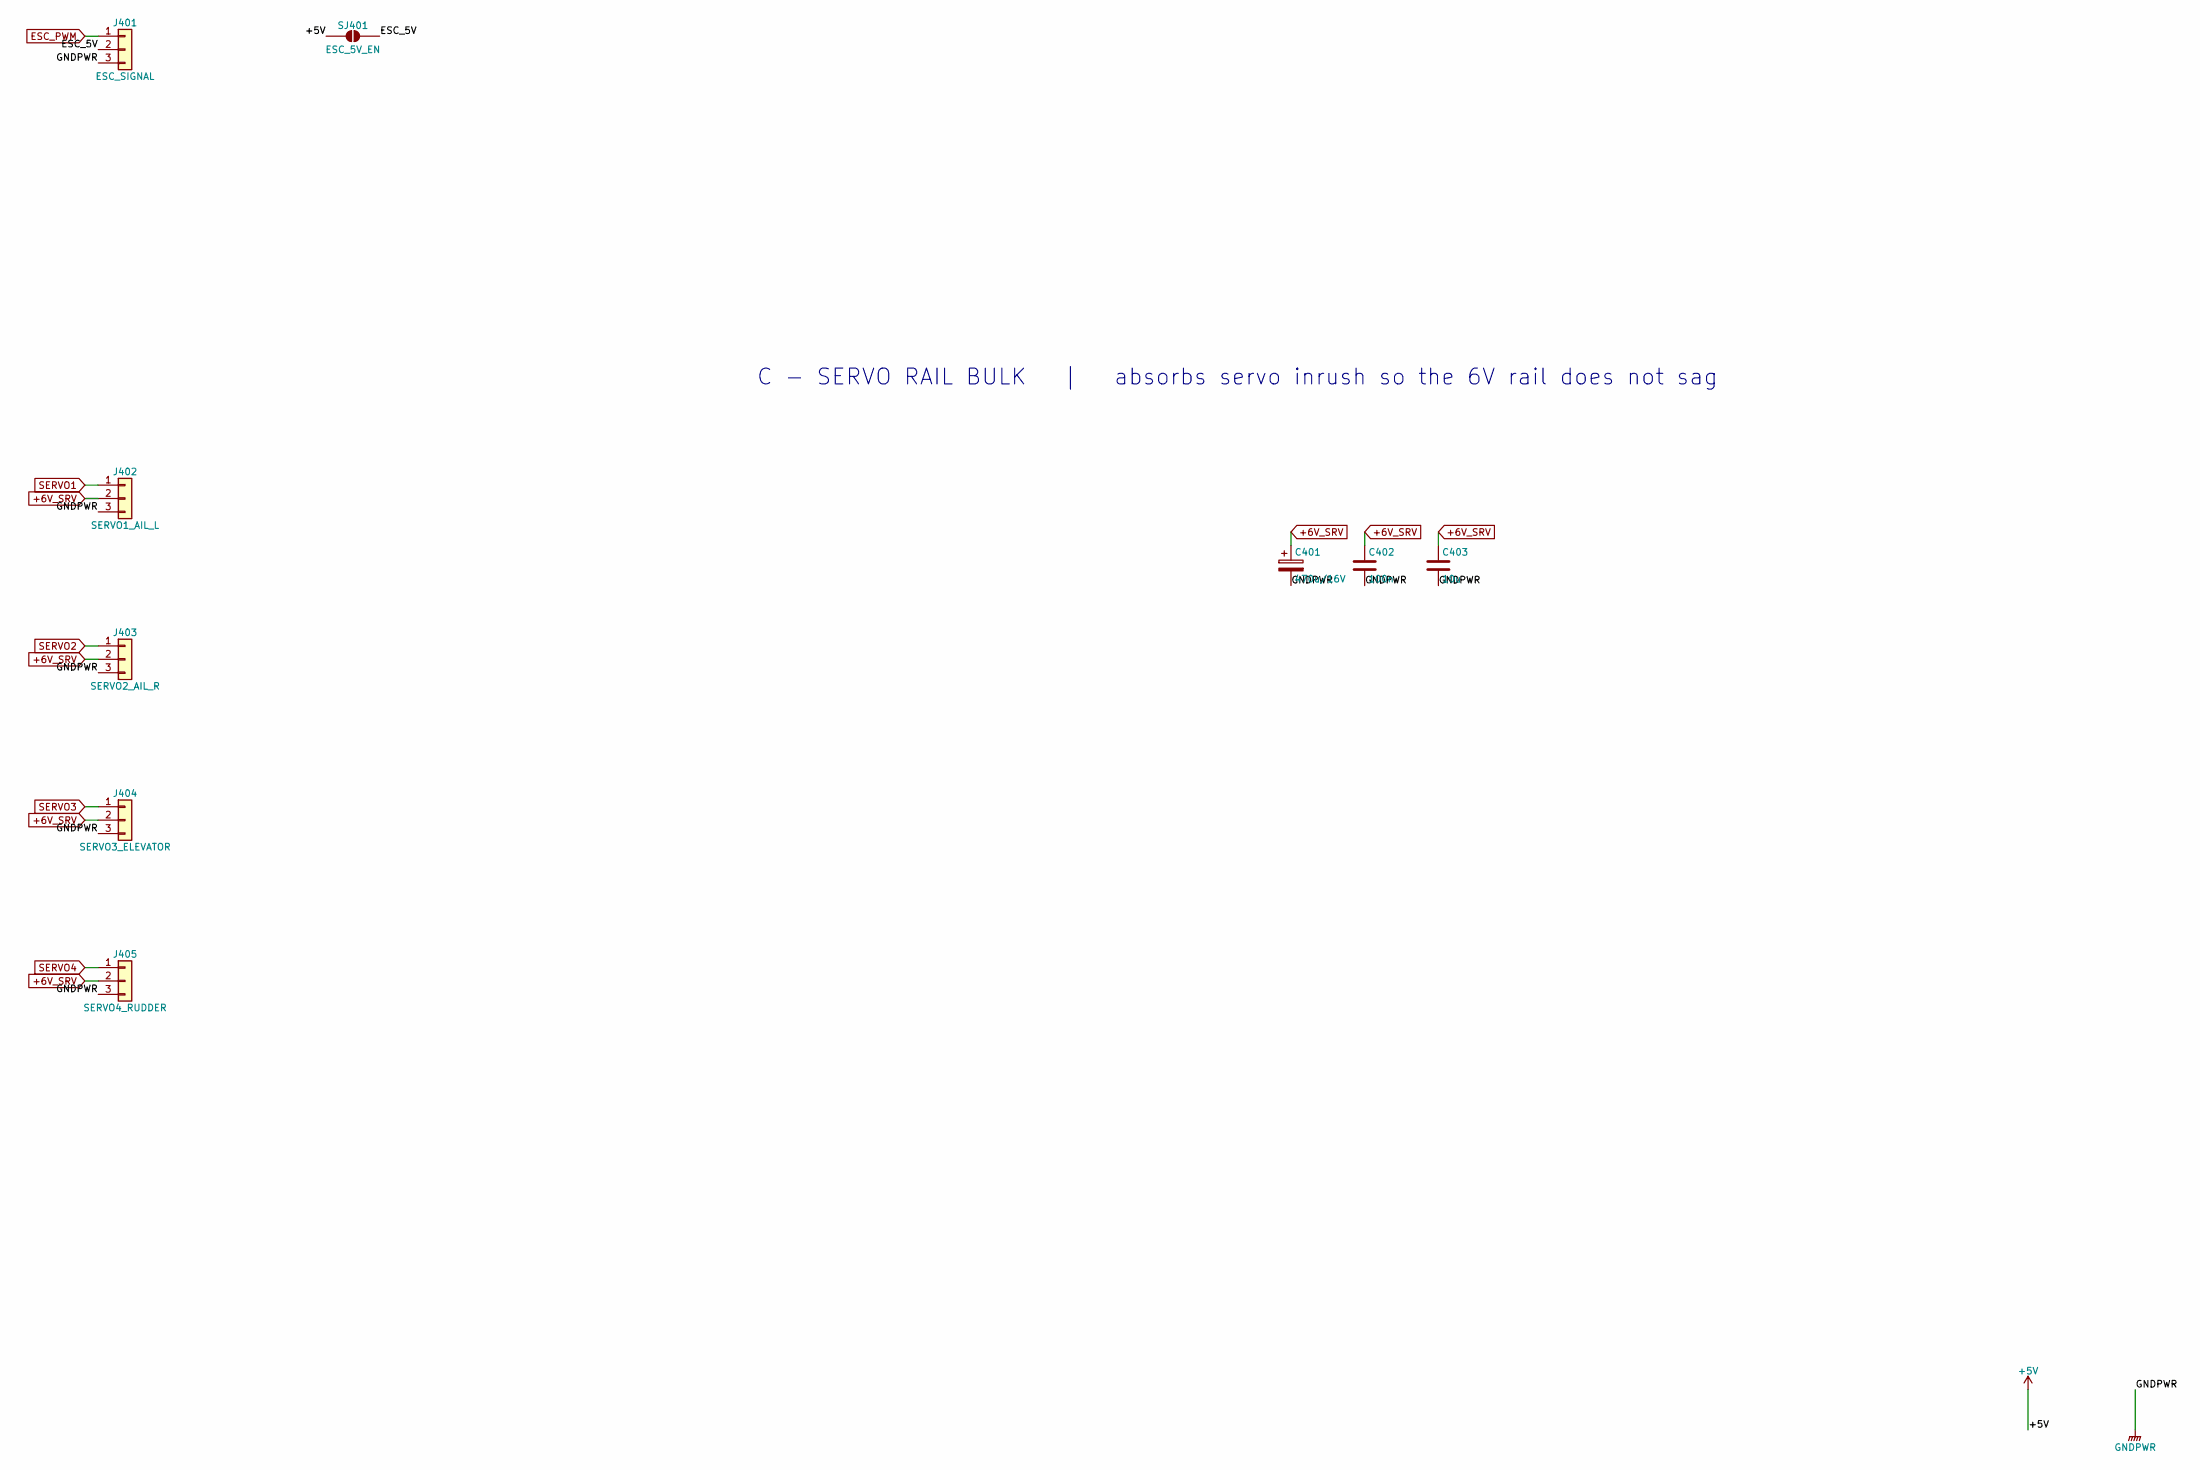
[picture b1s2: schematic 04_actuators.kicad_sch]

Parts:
C401: 470u/16V; CP_Elec_8x10.5
C402: 100n; C_0603_1608Metric
C403: 10u; C_1210_3225Metric
J401: ESC_SIGNAL; PinHeader_1x03_P2.54mm_Vertical
J402: SERVO1_AIL_L; PinHeader_1x03_P2.54mm_Vertical
J403: SERVO2_AIL_R; PinHeader_1x03_P2.54mm_Vertical
J404: SERVO3_ELEVATOR; PinHeader_1x03_P2.54mm_Vertical
J405: SERVO4_RUDDER; PinHeader_1x03_P2.54mm_Vertical
SJ401: ESC_5V_EN; SolderJumper-2_P1.3mm_Open_Pad1.0x1.5mm

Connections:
/04_ACTUATORS/ESC_5V: J401.2, SJ401.2 (B)
ESC_PWM: J401.1; also elsewhere on the board
SERVO1: J402.1; also elsewhere on the board
SERVO2: J403.1; also elsewhere on the board
SERVO3: J404.1; also elsewhere on the board
SERVO4: J405.1; also elsewhere on the board

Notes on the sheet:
C - SERVO RAIL BULK | absorbs servo inrush so the 6V rail does not sag

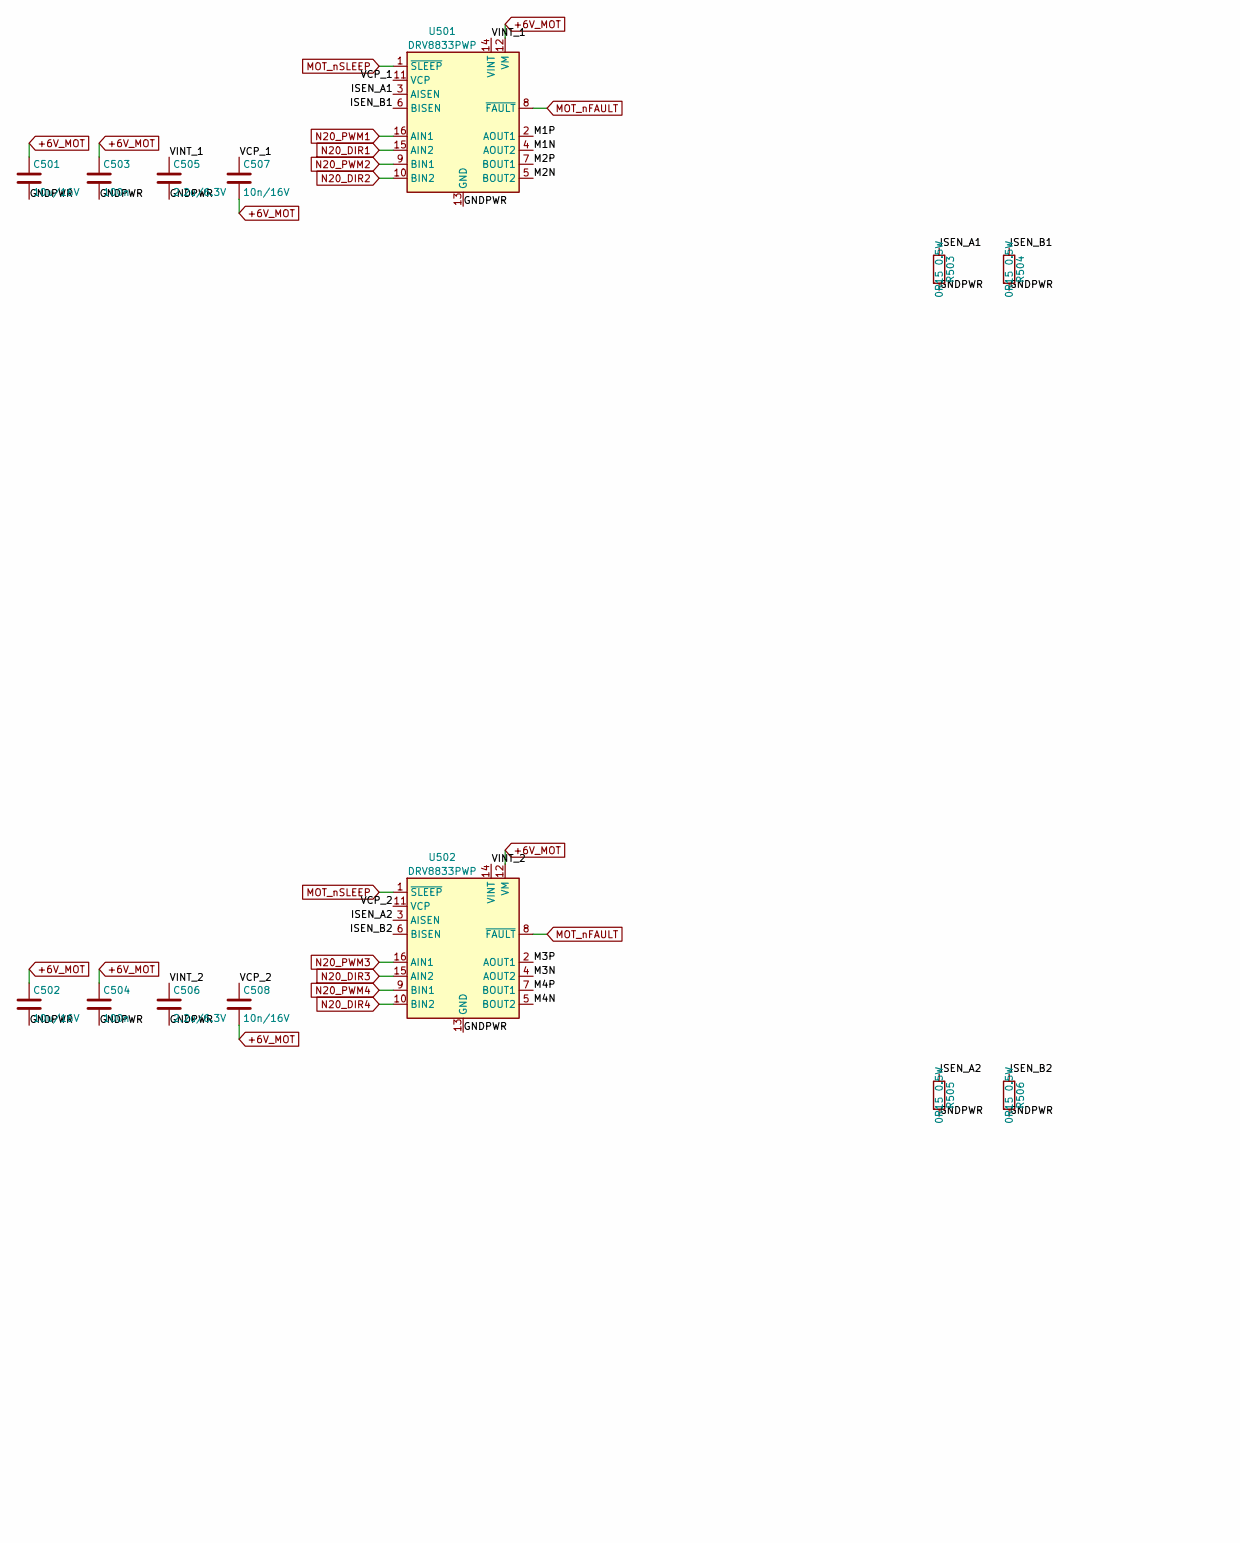
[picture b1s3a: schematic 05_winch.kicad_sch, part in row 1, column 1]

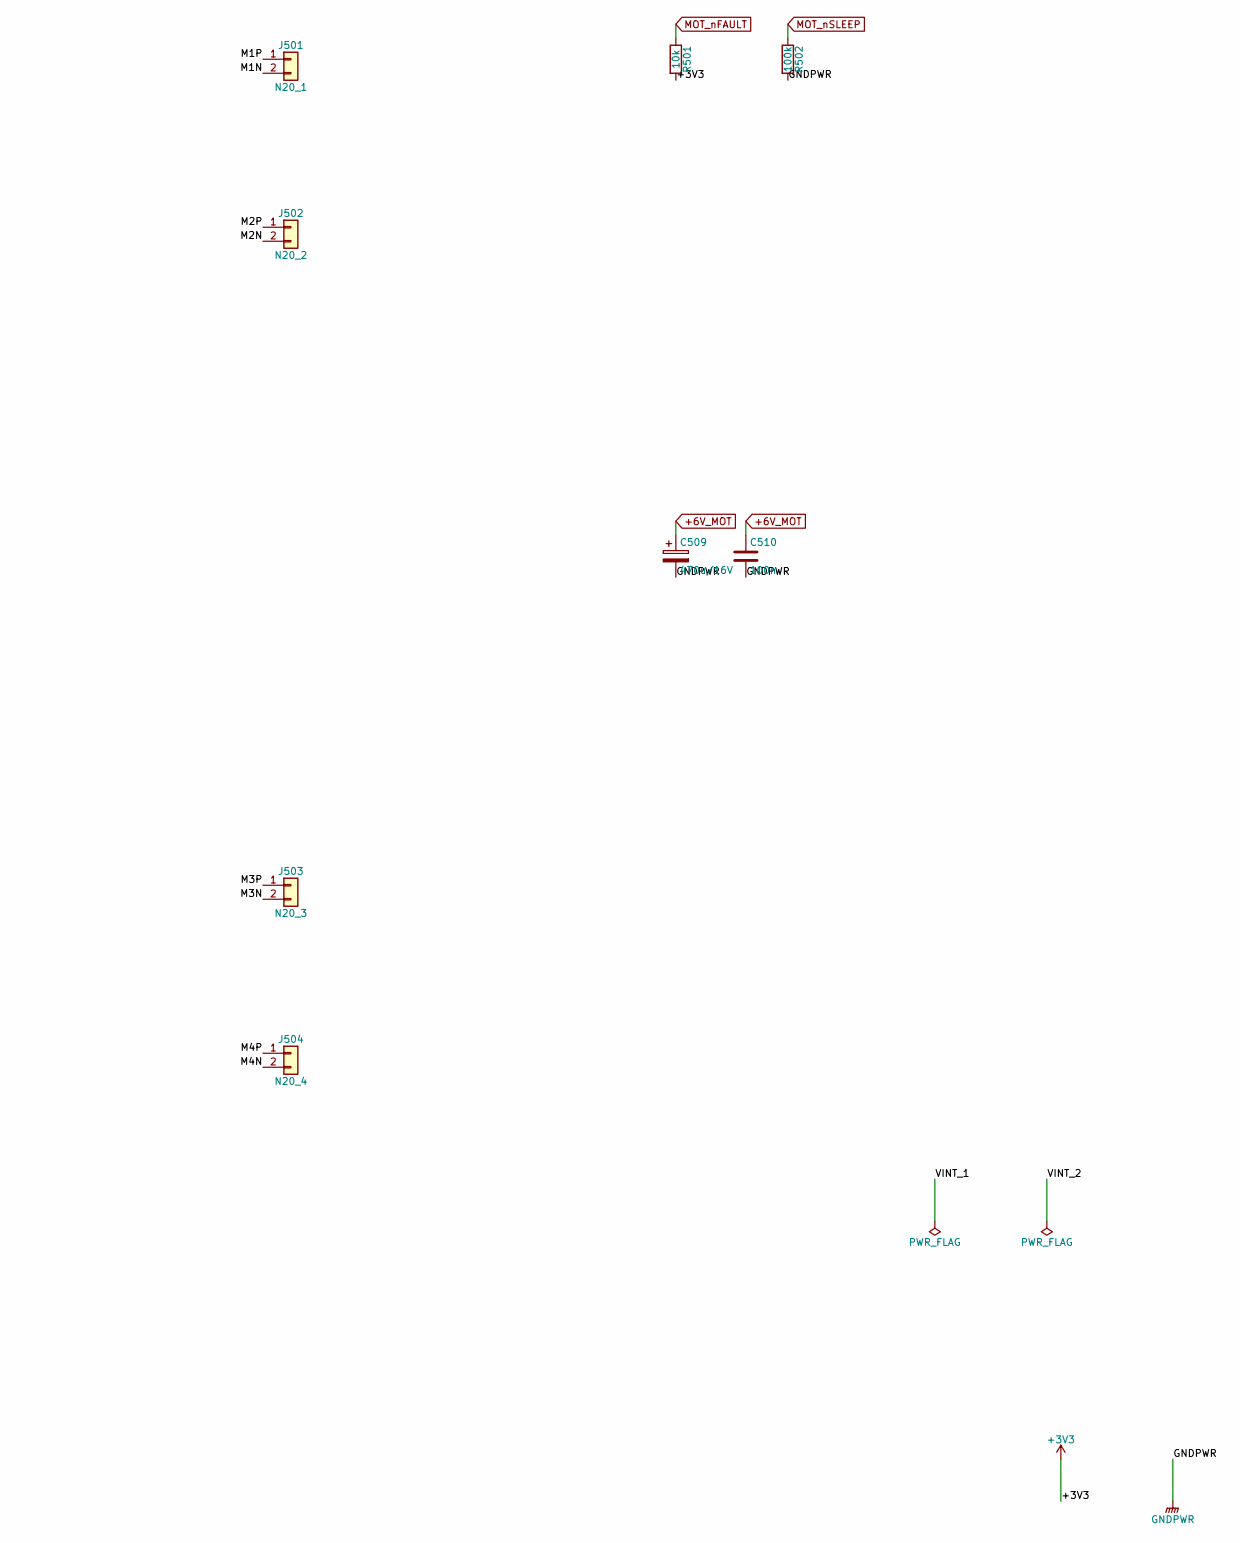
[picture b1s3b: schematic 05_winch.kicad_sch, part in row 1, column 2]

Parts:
C501, C502: 10u/16V; C_1210_3225Metric
C503, C504, C510: 100n; C_0603_1608Metric
C505, C506: 2.2u/6.3V; C_0603_1608Metric
C507, C508: 10n/16V; C_0603_1608Metric
C509: 470u/16V; CP_Elec_8x10.5
J501: N20_1; JST_PH_S2B-PH-K_1x02_P2.00mm_Horizontal
J502: N20_2; JST_PH_S2B-PH-K_1x02_P2.00mm_Horizontal
J503: N20_3; JST_PH_S2B-PH-K_1x02_P2.00mm_Horizontal
J504: N20_4; JST_PH_S2B-PH-K_1x02_P2.00mm_Horizontal
R501: 10k; R_0603_1608Metric
R502: 100k; R_0603_1608Metric
R503, R504, R505, R506: 0R15 0.5W; R_1206_3216Metric
U501, U502: DRV8833PWP; HTSSOP-16-1EP_4.4x5mm_P0.65mm_EP3.4x5mm_Mask2.46x2.31mm_The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

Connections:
/05_WINCH/ISEN_A1: R503.1, U501.3 (AISEN)
/05_WINCH/ISEN_A2: R505.1, U502.3 (AISEN)
/05_WINCH/ISEN_B1: R504.1, U501.6 (BISEN)
/05_WINCH/ISEN_B2: R506.1, U502.6 (BISEN)
/05_WINCH/M1N: J501.2, U501.4 (AOUT2)
/05_WINCH/M1P: J501.1, U501.2 (AOUT1)
/05_WINCH/M2N: J502.2, U501.5 (BOUT2)
/05_WINCH/M2P: J502.1, U501.7 (BOUT1)
/05_WINCH/M3N: J503.2, U502.4 (AOUT2)
/05_WINCH/M3P: J503.1, U502.2 (AOUT1)
/05_WINCH/M4N: J504.2, U502.5 (BOUT2)
/05_WINCH/M4P: J504.1, U502.7 (BOUT1)
/05_WINCH/VCP_1: C507.1, U501.11 (VCP)
/05_WINCH/VCP_2: C508.1, U502.11 (VCP)
MOT_nFAULT: R501.1, U501.8 (~FAULT), U502.8 (~FAULT); also elsewhere on the board
MOT_nSLEEP: R502.1, U501.1 (~SLEEP), U502.1 (~SLEEP); also elsewhere on the board
N20_DIR1: U501.15 (AIN2); also elsewhere on the board
N20_DIR2: U501.10 (BIN2); also elsewhere on the board
N20_DIR3: U502.15 (AIN2); also elsewhere on the board
N20_DIR4: U502.10 (BIN2); also elsewhere on the board
N20_PWM1: U501.16 (AIN1); also elsewhere on the board
N20_PWM2: U501.9 (BIN1); also elsewhere on the board
N20_PWM3: U502.16 (AIN1); also elsewhere on the board
N20_PWM4: U502.9 (BIN1); also elsewhere on the board
